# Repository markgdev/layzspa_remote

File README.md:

# LayZSpa 4 Pin Serial ESP8266 Controller
An NodeMCU/ESP8266 controller for the 4 pin version of the LayZSpa, specifically designed and tested for a 2018 LayZSpa Hawaii.

## Prototype PCB/Schematic
Located within the pcb directory are the eagle files I used to get the prototype PCB board. Hopefully the schematic below is useful to you even without the PCB.

Note that the version in here is yet to be printed as there was an error in the first version. It is however possible to set this up without a PCB, however I found it a little messy and difficult to manage when working within the pump unit.

### Schematic

### Bill of materials
- NodeMCU V3 (Note there are other versions of NodeMCU that will not fit this printed PCB, v3 has v0.1 printed in the top right corner)
- 4 Channel bi-directional logic level shifter
- 4 pin dupoint connectors (2x)
- 4 pin JST-SM Female to terminate to dupoont
- 4 pin JST-SM Male to terminate to dupont

### Notes
- With 4 pin connectors at top of board, left side connects to DSP, right to IOC.
- Pin 1 of each connector is 5v
- Pin 4 of each connector is GND

There is a seperate 3 pin header which I plan to use in the future to connect a DS18b20 temperature sensor to give more precise temperature measurement to avoid large swings in temperature.

## Arduino Sketch
Flash your NodeMCU device with the sketch located in esp8266_sketch

Connect your PCB/NodeMCU to the pump unit with the JST-SM connectors.

Once you have flashed the device it will host a simple (needs to be improved) web interface to allow control.

http://\<ipaddress\>/

Set the desired temperature and turn on heater general to start heating/pump.

The air blower currently is only controlled through the top panel of the pump. **Note that you will loose all other control from the pump control panel!**

Unlike the standard controller the sketch will currently turn the heater back on/off as soon as the tempurature goes outside of the set temp.

There is also a json output avaiable at http://\<ipaddress\>/status, I have used a combination of this and the above address with the parameters you see when you press a button to develop a home assistant climate integration, more details below...

### ximon Hot Tub Remote
I made great use of the information on the below issue to get this working, my work is very much still in protoype and I plan to contribute back to the idea of a generic setup across the LayZSpa variants, as talked about. You may notice that the status endpoint is already the as similar as it can be. I'll work to add the other endpoints soon.

https://github.com/ximon/Hot-tub-remote/issues/4#issuecomment-753403581

## Home Assistant Installation
Clone this repo

Copy custom_components/layzspa to <homeassistant config>/custom_components/layzspa

Or Use HACS

### Configuration
```yaml
climate:
  - platform: layzspa
    ipaddr: 192.168.1.178
```

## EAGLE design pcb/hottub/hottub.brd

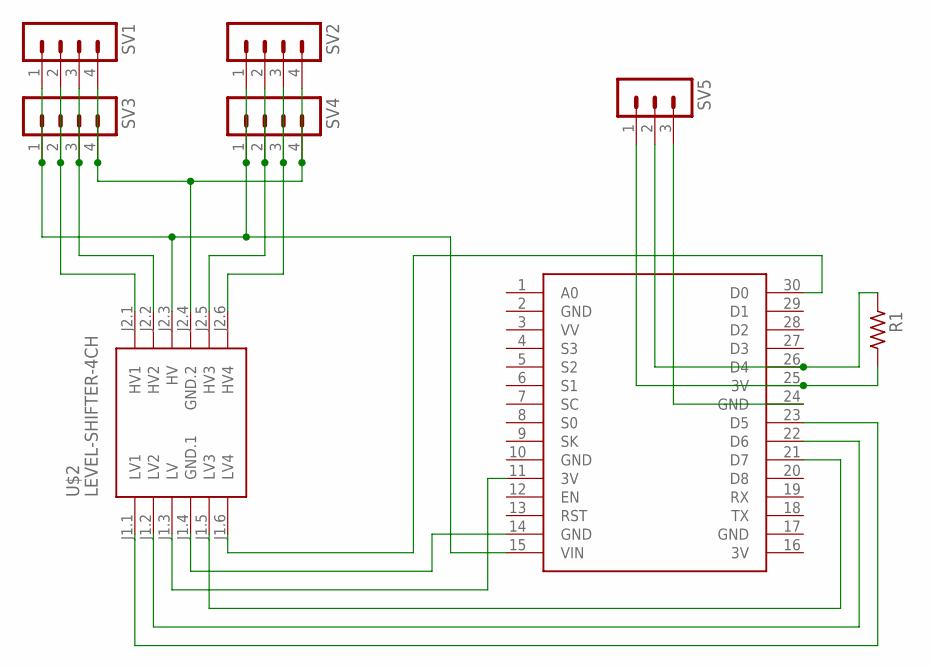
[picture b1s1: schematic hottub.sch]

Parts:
R1: R_1206; R1206
SV1, SV2, SV3, SV4: MA04-1
SV5: MA03-1
U$1: NODEMCU
U$2: LEVEL-SHIFTER-4CH

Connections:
3V: U$1.16 (3V)
GND: U$1.2 (GND), U$1.10 (GND), U$1.17 (GND)
unnamed: R1.2, SV5.1, U$1.25 (3V)
unnamed: SV1.2, SV3.2, U$2.J2.1 (HV1)
unnamed: SV1.3, SV3.3, U$2.J2.2 (HV2)
unnamed: SV5.3, U$1.24 (GND)
unnamed: U$1.14 (GND), U$2.J1.4 (GND.1)
unnamed: SV1.1, SV2.1, SV3.1, SV4.1, U$1.15 (VIN), U$2.J2.3 (HV)
unnamed: SV2.2, SV4.2, U$2.J2.5 (HV3)
unnamed: U$1.30 (D0), U$2.J1.6 (LV4)
unnamed: U$1.21 (D7), U$2.J1.5 (LV3)
unnamed: U$1.22 (D6), U$2.J1.2 (LV2)
unnamed: U$1.23 (D5), U$2.J1.1 (LV1)
unnamed: SV2.3, SV4.3, U$2.J2.6 (HV4)
unnamed: SV1.4, SV2.4, SV3.4, SV4.4, U$2.J2.4 (GND.2)
unnamed: R1.1, SV5.2, U$1.26 (D4)
unnamed: U$1.11 (3V), U$2.J1.3 (LV)

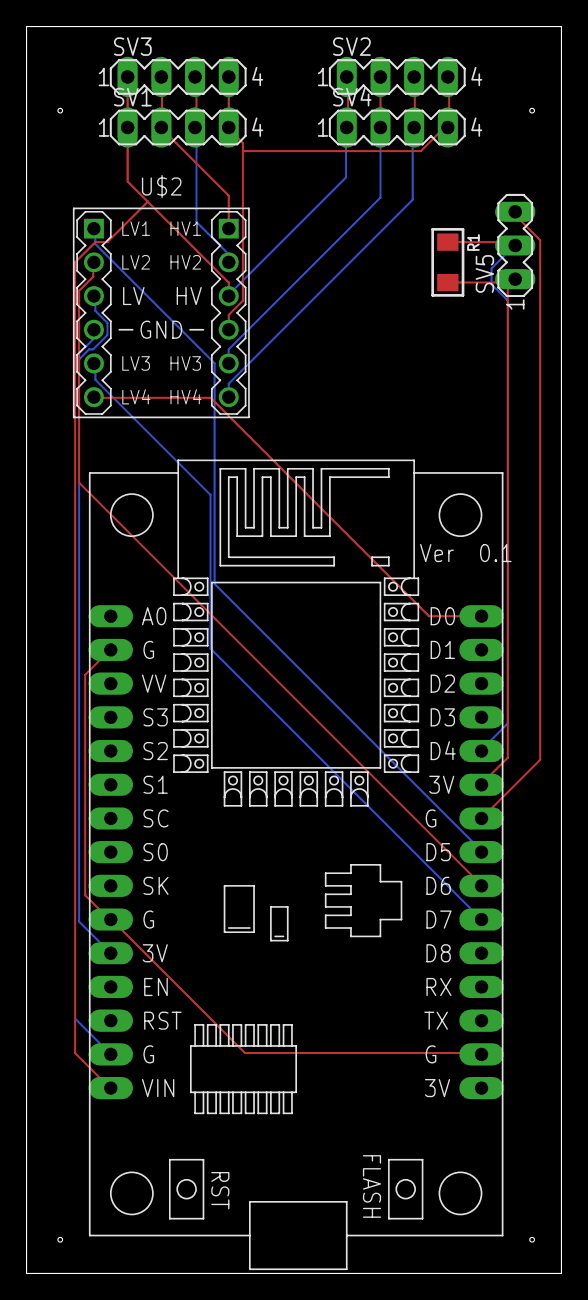
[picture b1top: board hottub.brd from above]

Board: 2 copper layers, 40.3 x 94.0 mm, 8 parts (0 on the bottom side), 16 nets.

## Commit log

2021-01-04 Added schematic image

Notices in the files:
parts and their libraries:
diy-modules: Released under the Creative Commons Attribution 4.0 International License: http://creativecommons.org/licenses/by/4.0
rc-master-smd: Copyright (C) 2007, Bob Starr
